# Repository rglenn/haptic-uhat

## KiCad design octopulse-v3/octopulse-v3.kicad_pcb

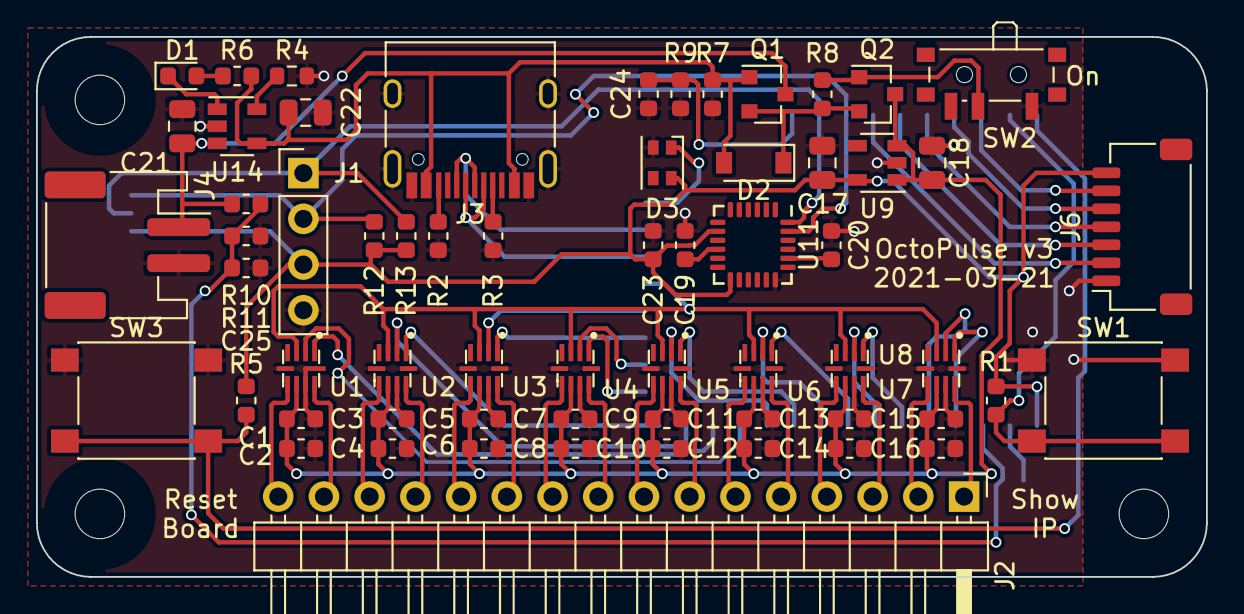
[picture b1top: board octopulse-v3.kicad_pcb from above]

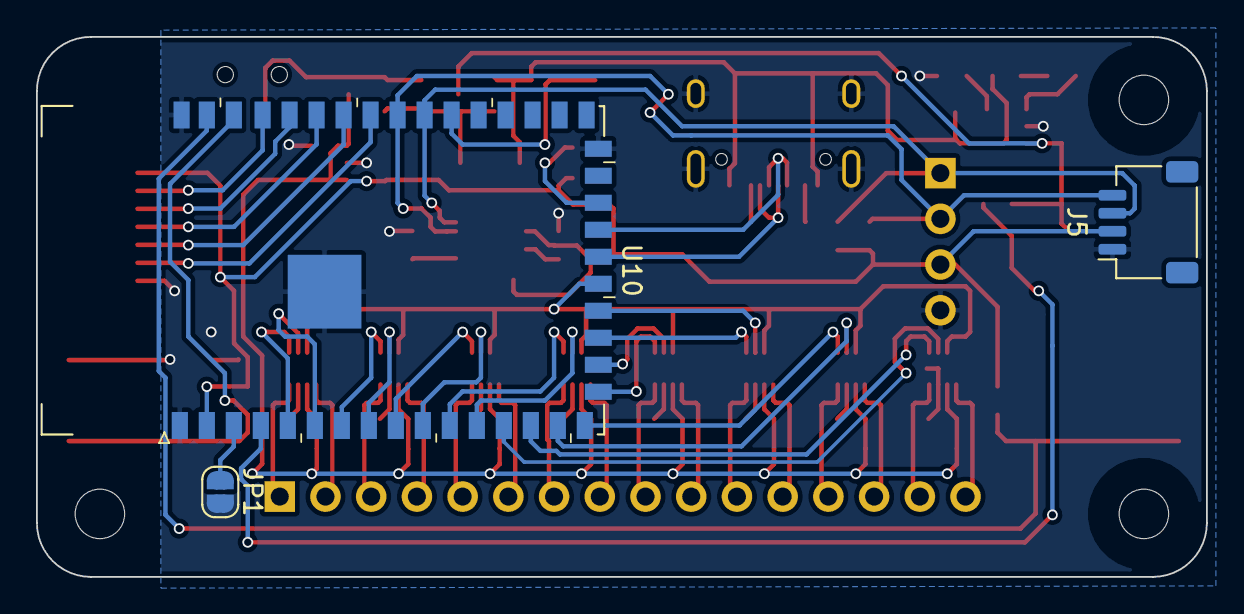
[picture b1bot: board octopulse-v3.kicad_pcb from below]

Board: 2 copper layers, 65.0 x 30.0 mm, 65 parts (3 on the bottom side), 62 nets.

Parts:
C1, C3, C5, C7, C9, C11, C13, C15, C19, C23, C25: 100n; C_0603_1608Metric
C2, C4, C6, C8, C10, C12, C14, C16, C24: 1u; C_0603_1608Metric
C17: 22u; C_0805_2012Metric
C18, C21, C22: 10u; C_0805_2012Metric
C20: 2.2n; C_0603_1608Metric
D1: LED; LED_0603_1608Metric
D2: B5819W; D_SOD-123
D3: TC2020RGB-3CJH
J1: Conn_01x04_Male; PinHeader_1x04_P2.54mm_Vertical
J2: Conn_01x16_Male; PinHeader_1x16_P2.54mm_Horizontal
J3: USB_C_Receptacle_USB2.0; USB_C_Receptacle_HRO_TYPE-C-31-M-12
J4: Conn_01x02; JST_PH_S2B-PH-SM4-TB_1x02-1MP_P2.00mm_Horizontal
J5: Conn_01x04; JST_SH_SM04B-SRSS-TB_1x04-1MP_P1.00mm_Horizontal
J6: Conn_01x07; JST_SH_SM07B-SRSS-TB_1x07-1MP_P1.00mm_Horizontal
JP1: SolderJumper_2_Open; SolderJumper-2_P1.3mm_Open_RoundedPad1.0x1.5mm
Q1, Q2: DMG3415U; SOT-23
R1, R5: 10K; R_0603_1608Metric
R2, R3: 5.1K; R_0603_1608Metric
R4: 3.3K; R_0603_1608Metric
R6: 1K; R_0603_1608Metric
R7, R8: 100K; R_0603_1608Metric
R9, R10, R11: 1M; R_0603_1608Metric
R12, R13: 4.7K; R_0603_1608Metric
SW1, SW3: SW_Push; SW_SPST_PTS645
SW2: SW_SPDT; SW_SPDT_PCM12
U1, U2, U3, U4, U5, U6, U7, U8: DRV2603; QFN50P200X200X80-10N
U9: AP2112K-3.3; SOT-23-5
U10: ESP32-S2-WROVER
U11: MPU-6050; InvenSense_QFN-24_4x4mm_P0.5mm
U14: TP4054_[C32574]; SOT-23-5

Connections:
+3V3: C17.1, C23.1, D3.2, J1.3, J5.2, J6.7, R1.1, R5.1, R12.1, R13.1, U9.5, U10.2, U11.8, U11.13
/BATTMON: C25.1, R10.2, R11.1, U10.4
/BOOT0: JP1.1, U10.3
/D+: J3.A6, J3.B6, U10.23
/D-: J3.A7, J3.B7, U10.22
/DBLTAP: C24.1, R9.1, U10.32
/EN0: U1.1, U10.14
/EN1: U2.1, U10.16
/EN2: U3.1, U10.19
/EN3: U4.1, U10.17
/EN4: U5.1, U10.11
/EN5: U6.1, U10.9
/EN6: U7.1, U10.7
/EN7: U8.1, U10.5
/GPIO41: J6.2, U10.35
/GPIO42: J6.3, U10.36
/GPIO45: J6.6, U10.39
/IP_BTN: R1.2, SW1.2, U10.40
/LRA: U1.3, U2.3, U3.3, U4.3, U5.3, U6.3, U7.3, U8.3, U10.21
/MOT+0: J2.15, U1.9
/MOT+1: J2.13, U2.9
/MOT+2: J2.11, U3.9
/MOT+3: J2.9, U4.9
/MOT+4: J2.7, U5.9
/MOT+5: J2.5, U6.9
/MOT+6: J2.3, U7.9
/MOT+7: J2.1, U8.9
/MOT-0: J2.16, U1.6
/MOT-1: J2.14, U2.6
/MOT-2: J2.12, U3.6
/MOT-3: J2.10, U4.6
/MOT-4: J2.8, U5.6
/MOT-5: J2.6, U6.6
/MOT-6: J2.4, U7.6
/MOT-7: J2.2, U8.6
/PWM0: U1.2, U10.13
/PWM1: U2.2, U10.15
/PWM2: U3.2, U10.20
/PWM3: U4.2, U10.18
/PWM4: U5.2, U10.12
/PWM5: U6.2, U10.10
/PWM6: U7.2, U10.8
/PWM7: U8.2, U10.6
/RESET: R5.2, SW3.2, U10.41
/RXD: J6.5, U10.38
/SCL: J1.2, J5.4, R12.2, U10.34, U11.23
/SDA: J1.1, J5.3, R13.2, U10.33, U11.24
/STATUSLED: D3.1, U10.24
/TXD: J6.4, U10.37
/VBAT: C21.1, J4.1, Q1.3, R10.1, U14.3
GND: C1.2, C2.2, C3.2, C4.2, C5.2, C6.2, C7.2, C8.2, C9.2, C10.2, C11.2, C12.2, C13.2, C14.2, C15.2, C16.2, C17.2, C18.2, C19.2, C20.2, C21.2, C22.2, C23.2, C24.2, C25.2, D3.4, J1.4, J3.A1, J3.A12, J3.B1, J3.B12, J3.S1, J4.2, J5.1, J6.1, JP1.2, R2.2, R3.2, R4.2, R7.1, R9.2, R11.2, SW1.1, SW2.1, SW3.1, U1.5, U1.8, U1.10, U2.5, U2.8, U2.10, U3.5, U3.8, U3.10, U4.5, U4.8, U4.10, U5.5, U5.8, U5.10, U6.5, U6.8, U6.10, U7.5, U7.8, U7.10, U8.5, U8.8, U8.10, U9.2, U10.1, U10.26, U10.42, U10.43, U11.18, U14.2
unnamed: C19.1, U11.10
unnamed: C20.1, U11.20
unnamed: D1.1, U14.1
unnamed: D1.2, R6.1
unnamed: D2.1, Q1.2, Q2.2, R8.1
unnamed: J3.A5, R3.1
unnamed: J3.B5, R2.1
unnamed: Q2.1, R8.2, SW2.2
unnamed: R4.1, U14.5
VBUS: C22.1, D2.2, J3.A4, J3.A9, J3.B4, J3.B9, Q1.1, R6.2, R7.2, U14.4
VDD: C1.1, C2.1, C3.1, C4.1, C5.1, C6.1, C7.1, C8.1, C9.1, C10.1, C11.1, C12.1, C13.1, C14.1, C15.1, C16.1, C18.1, Q2.3, U1.7, U2.7, U3.7, U4.7, U5.7, U6.7, U7.7, U8.7, U9.1, U9.3

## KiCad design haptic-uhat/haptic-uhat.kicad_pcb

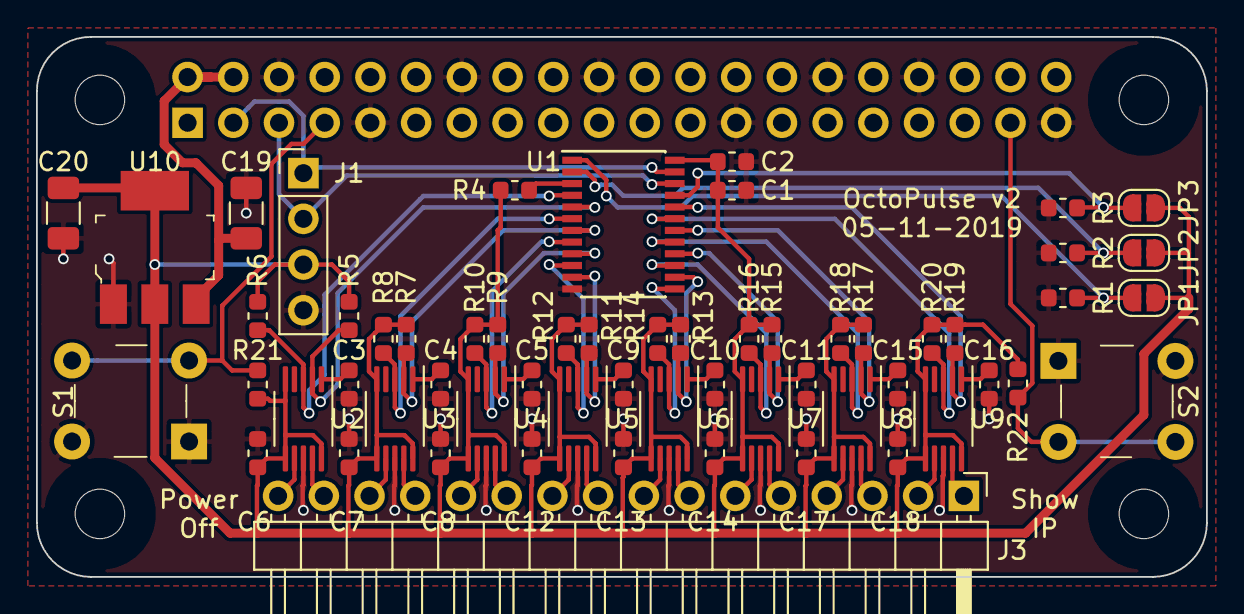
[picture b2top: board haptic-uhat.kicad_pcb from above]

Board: 2 copper layers, 65.0 x 30.0 mm, 60 parts (1 on the bottom side), 51 nets.

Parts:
C1: 100n; C_0603_1608Metric
C2, C3, C4, C5, C6, C7, C8, C9, C10, C11, C12, C13, C14, C15, C16, C17, C18: 1u; C_0603_1608Metric
C19: 10u; C_1206_3216Metric
C20: 22u; C_1206_3216Metric
J1: Conn_01x04_Male; PinHeader_1x04_P2.54mm_Vertical
J2: RPi_GPIO; PinSocket_2x20_P2.54mm_Vertical
J3: Conn_01x16_Male; PinHeader_1x16_P2.54mm_Horizontal
JP1, JP2, JP3: SolderJumper_2_Open; SolderJumper-2_P1.3mm_Open_RoundedPad1.0x1.5mm
R1, R2, R3, R4, R21, R22: 10K; R_0603_1608Metric
R5, R6, R7, R8, R9, R10, R11, R12, R13, R14, R15, R16, R17, R18, R19, R20: 4.7K; R_0603_1608Metric
S1, S2: B3F-1000; Switch_Tactile_THT_B3F-1xxx
U1: TCA9548APW; TSSOP-24_4.4x7.8mm_P0.65mm
U2, U3, U4, U5, U6, U7, U8, U9: DRV2605L; VSSOP-10_3x3mm_P0.5mm
U10: AZ1117CH-3_3TRG1; SOT-223

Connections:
+3V3: C1.1, C2.1, C6.1, C7.1, C8.1, C12.1, C13.1, C14.1, C17.1, C18.1, C20.1, J1.3, JP1.1, JP2.1, JP3.1, R4.1, R5.1, R6.1, R7.1, R8.1, R9.1, R10.1, R11.1, R12.1, R13.1, R14.1, R15.1, R16.1, R17.1, R18.1, R19.1, R20.1, R21.1, R22.1, U1.24, U2.5, U2.6, U2.10, U3.5, U3.6, U3.10, U4.5, U4.6, U4.10, U5.5, U5.6, U5.10, U6.5, U6.6, U6.10, U7.5, U7.6, U7.10, U8.5, U8.6, U8.10, U9.5, U9.6, U9.10, U10.2, U10.4
+5V: C19.1, J2.2, J2.4, U10.3
/A0: JP1.2, R1.1, U1.1
/A1: JP2.2, R2.1, U1.2
/A2: JP3.2, R3.1, U1.21
/IP_BTN: J2.37, R22.2, S2.3, S2.4
/MOT+0: J3.16, U2.7
/MOT+1: J3.14, U3.7
/MOT+2: J3.12, U4.7
/MOT+3: J3.10, U5.7
/MOT+4: J3.8, U6.7
/MOT+5: J3.6, U7.7
/MOT+6: J3.4, U8.7
/MOT+7: J3.2, U9.7
/MOT-0: J3.15, U2.9
/MOT-1: J3.13, U3.9
/MOT-2: J3.11, U4.9
/MOT-3: J3.9, U5.9
/MOT-4: J3.7, U6.9
/MOT-5: J3.5, U7.9
/MOT-6: J3.3, U8.9
/MOT-7: J3.1, U9.9
/SCL0: R5.2, U1.5, U2.2
/SCL1: R7.2, U1.7, U3.2
/SCL2: R9.2, U1.9, U4.2
/SCL3: R11.2, U1.11, U5.2
/SCL4: R13.2, U1.14, U6.2
/SCL5: R15.2, U1.16, U7.2
/SCL6: R17.2, U1.18, U8.2
/SCL7: R19.2, U1.20, U9.2
/SCL_PI: J1.2, J2.5, U1.22
/SDA0: R6.2, U1.4, U2.3
/SDA1: R8.2, U1.6, U3.3
/SDA2: R10.2, U1.8, U4.3
/SDA3: R12.2, U1.10, U5.3
/SDA4: R14.2, U1.13, U6.3
/SDA5: R16.2, U1.15, U7.3
/SDA6: R18.2, U1.17, U8.3
/SDA7: R20.2, U1.19, U9.3
/SDA_PI: J1.1, J2.3, U1.23
/SHDN_BTN: J2.7, R21.2, S1.3, S1.4
GND: C1.2, C2.2, C3.2, C4.2, C5.2, C6.2, C7.2, C8.2, C9.2, C10.2, C11.2, C12.2, C13.2, C14.2, C15.2, C16.2, C17.2, C18.2, C19.2, C20.2, J1.4, J2.6, J2.9, J2.14, J2.20, J2.25, J2.30, J2.34, J2.39, R1.2, R2.2, R3.2, S1.1, S1.2, S2.1, S2.2, U1.12, U2.8, U3.8, U4.8, U5.8, U6.8, U7.8, U8.8, U9.8, U10.1
unnamed: C3.1, U2.1
unnamed: C4.1, U3.1
unnamed: C5.1, U4.1
unnamed: C9.1, U5.1
unnamed: C10.1, U6.1
unnamed: C11.1, U7.1
unnamed: C15.1, U8.1
unnamed: C16.1, U9.1
unnamed: R4.2, U1.3

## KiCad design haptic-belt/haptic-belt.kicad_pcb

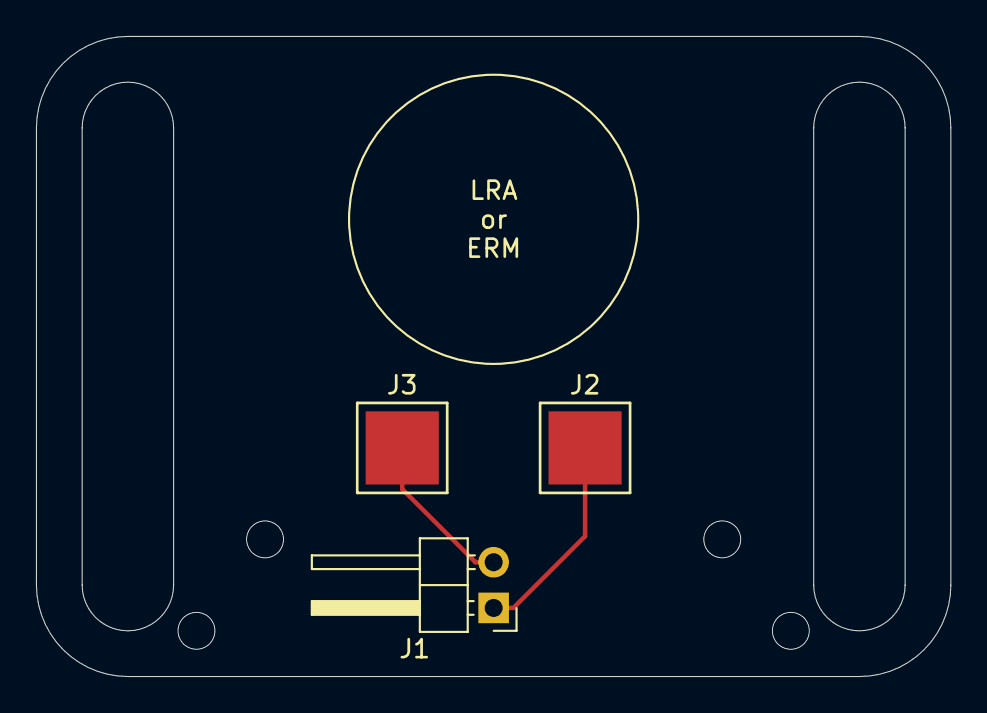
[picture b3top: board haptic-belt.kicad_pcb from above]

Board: 2 copper layers, 50.8 x 35.6 mm, 3 parts (0 on the bottom side), 2 nets.

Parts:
J1: Conn_01x02_Male; PinHeader_1x02_P2.54mm_Horizontal
J2, J3: Conn_01x01; 1Pin

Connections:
unnamed: J1.1, J2.1
unnamed: J1.2, J3.1

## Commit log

2019-09-29 Adding first rev of belt PCB
2019-09-29 Adding first rev of pi uhat PCB
2019-09-29 Adding PDF schematic and Gerber files for PCB manufacturing
2019-09-29 Adding 3D render
2019-09-29 Adding 3D render, PDF schematic, and manufacturing data for uhat
2019-11-06 Adds manufacturing data
2019-11-06 Updates hardware to version 2, which corrects backwards SDA/SCL, and adds second button for IP. Original button was wired to the same GPIO that the LiPo board uses to indicate low battery - we can us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
2019-11-06 Hey, guess what! The LiPo shim uses active-high on GPIO4 to indicate low battery. Swapped the button around to do the same. That would have been a fun one to debug...
2020-05-24 Adding enclosure for Pi done in OpenSCAD
2020-11-01 Adding octopulse code
2020-11-02 Adding IP display script
2020-11-02 Updating ip-display script and systemd config Updating octopulse-server systemd config
2020-11-03 Updating buzz_test to stop all buzzers when quitting
2020-11-04 Fixing delay limit issue in octopulse-server
2021-03-21 Adding V3 in progress
2021-03-23 I think this is everything. Hardware complete?
2021-04-03 We really should be using the LRA signal library with the LRAs, and not the ERM signal library.
